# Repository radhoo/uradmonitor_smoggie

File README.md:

# uradmonitor_smoggie
SMOGGIE is an ultra-low cost automated air quality monitor with a rain proof enclosure and a simple mount system to make installation easy. 

This repo includes all the blueprints needed to build Smoggie:
1) PCB shield for Wemos D1 Wifi module , plus a series of sensors: 
Particulate Matter: Plantower PMSA003, PMS5003, PMS6003, PMS7003, Winsen ZH03A, Cubic PM2009
CO2: Winsen MH-Z19B, Cubic CM1106, Mixsen 6010 NDIR CO2 sensors
Gas: Winsen ZE03
2) Code, Arduino compatible, including local webserver, HTTP Client and all the drivers for the sensors supported
3) 3d Printable enclosure (Either Filament/FDM or Resin/SLA)

See also:
- the [uRADMonitor SMOGGIE-PM](https://www.uradmonitor.com/products/#docs-6) product page, click on tab "Smoggie PM"
- [Technical Datasheet](https://www.uradmonitor.com/wp-content/uploads/2021/08/datasheet_smoggie_v5_compressed.pdf)

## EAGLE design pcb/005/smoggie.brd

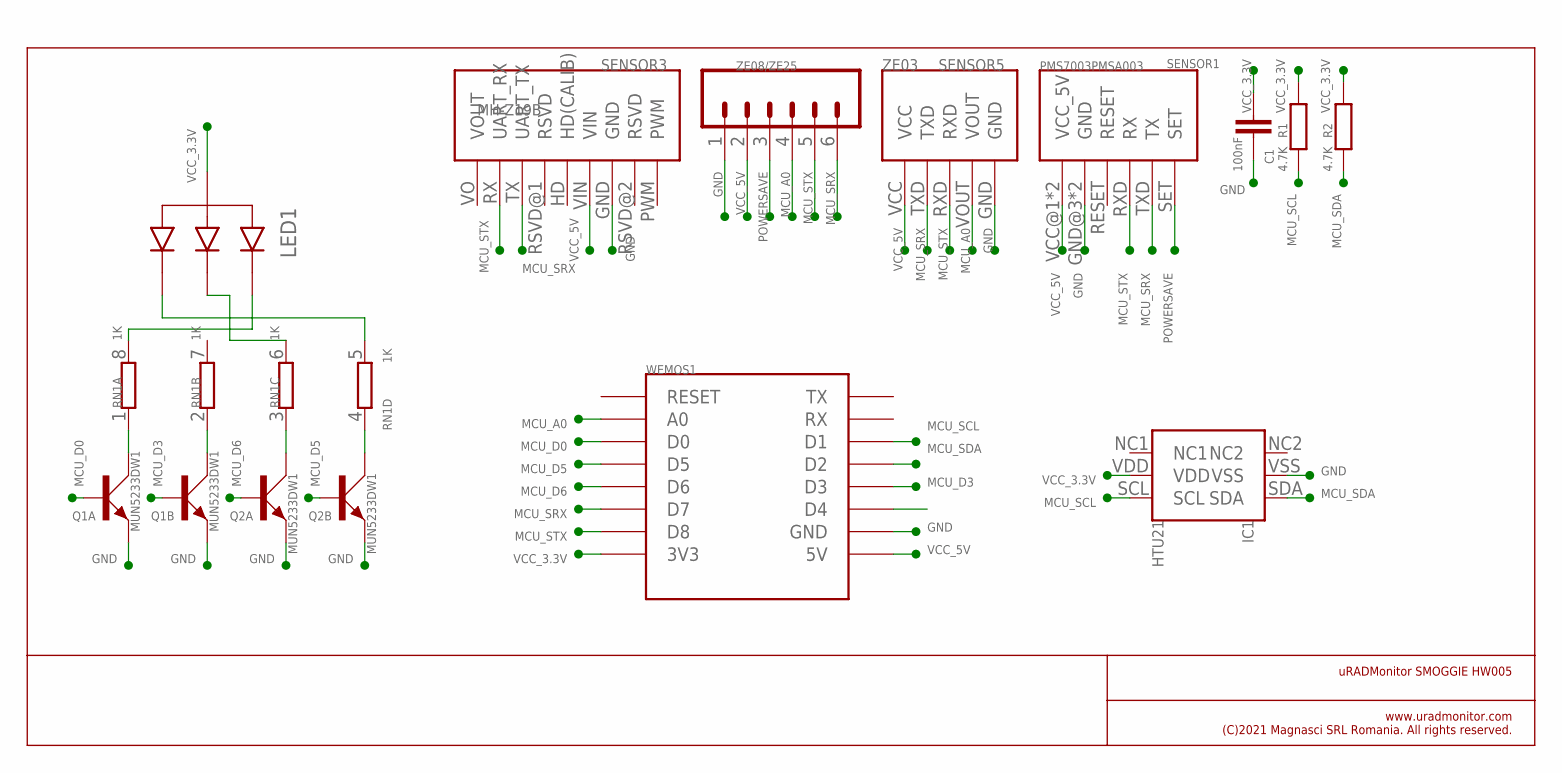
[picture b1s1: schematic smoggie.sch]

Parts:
C1: 100nF; C0603
IC1: HTU21; SHT21
LED1: LED_1615_RGB_CA; 1615_LED_CA
Q1, Q2: MUN5233DW1; SOT363_PHILIPS
R1, R2: 4.7K; R0603
RN1: 1K; 0603-ARC
SENSOR1: PMS7003PMSA003; PMSA003
SENSOR3: MH-Z19B
SENSOR5: ZE03
WEMOS1: 11; WEMOS-D1-MINI
ZE08/ZE25: M06SIP; 1X06

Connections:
GND: C1.1, IC1.VSS, Q1.1 (E), Q1.4 (E), Q2.1 (E), Q2.4 (E), SENSOR1.GND@3 (GND), SENSOR1.GND@4 (GND), SENSOR3.GND, SENSOR5.GND, WEMOS1.GND, ZE08/ZE25.1
MCU_A0: SENSOR5.VOUT, WEMOS1.A0, ZE08/ZE25.4
MCU_D0: Q1.2 (B), WEMOS1.D0
MCU_D3: Q1.5 (B), WEMOS1.D3
MCU_D5: Q2.5 (B), WEMOS1.D5
MCU_D6: Q2.2 (B), WEMOS1.D6
MCU_SCL: IC1.SCL, R1.2, WEMOS1.D1
MCU_SDA: IC1.SDA, R2.2, WEMOS1.D2
MCU_SRX: SENSOR1.TXD (TX), SENSOR3.TX (UART_TX), SENSOR5.TXD, WEMOS1.D7, ZE08/ZE25.6
MCU_STX: SENSOR1.RXD (RX), SENSOR3.RX (UART_RX), SENSOR5.RXD, WEMOS1.D8, ZE08/ZE25.5
unnamed: LED1.P$4 (P4_BLUE), RN1.8 (2)
unnamed: LED1.P$3 (P3_GREEN), RN1.6 (2)
unnamed: Q1.6 (C), RN1.1
unnamed: Q1.3 (C), RN1.2 (1)
unnamed: Q2.6 (C), RN1.3 (1)
unnamed: Q2.3 (C), RN1.4 (1)
unnamed: LED1.P$2 (P2_RED), RN1.5 (2)
POWERSAVE: SENSOR1.SET, ZE08/ZE25.3
VCC_3.3V: C1.2, IC1.VDD, LED1.P$1 (P1_CA), R1.1, R2.1, WEMOS1.3V3
VCC_5V: SENSOR1.VCC@1 (VCC_5V), SENSOR1.VCC@2 (VCC_5V), SENSOR3.VIN, SENSOR5.VCC, WEMOS1.5V, ZE08/ZE25.2

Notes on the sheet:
uRADMonitor SMOGGIE HW005
www.uradmonitor.com (C)2021 Magnasci SRL Romania. All rights reserved.

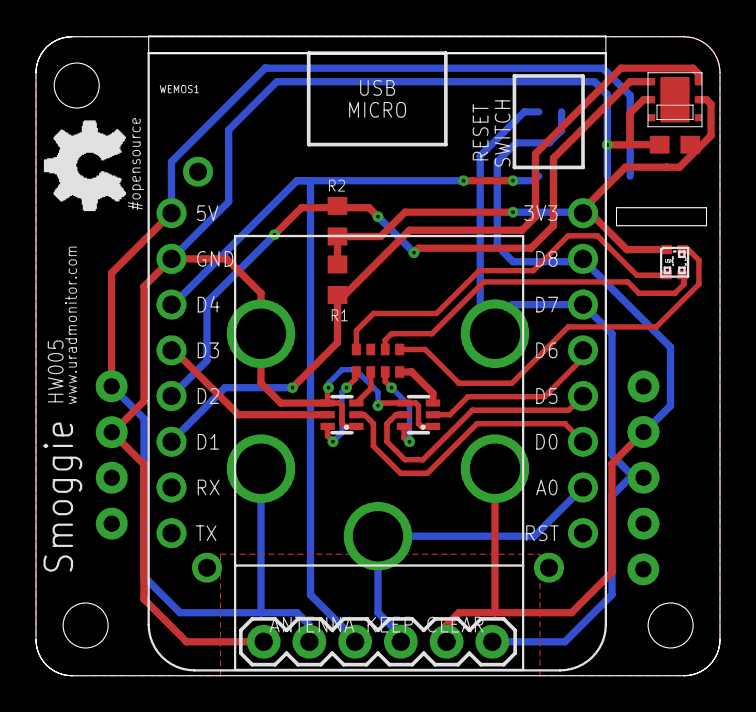
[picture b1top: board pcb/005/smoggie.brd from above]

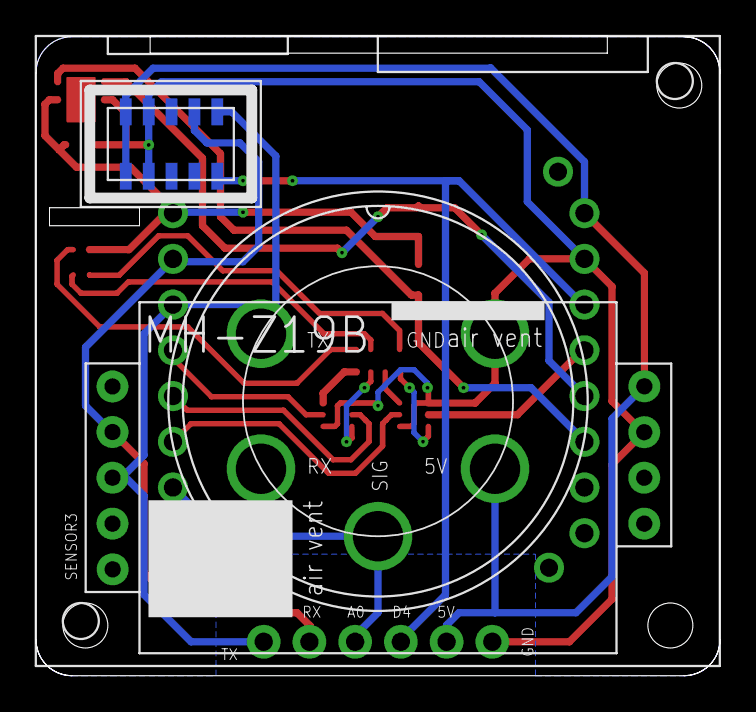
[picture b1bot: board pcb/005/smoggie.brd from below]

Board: 2 copper layers, 38.0 x 35.5 mm, 13 parts (3 on the bottom side), 20 nets.

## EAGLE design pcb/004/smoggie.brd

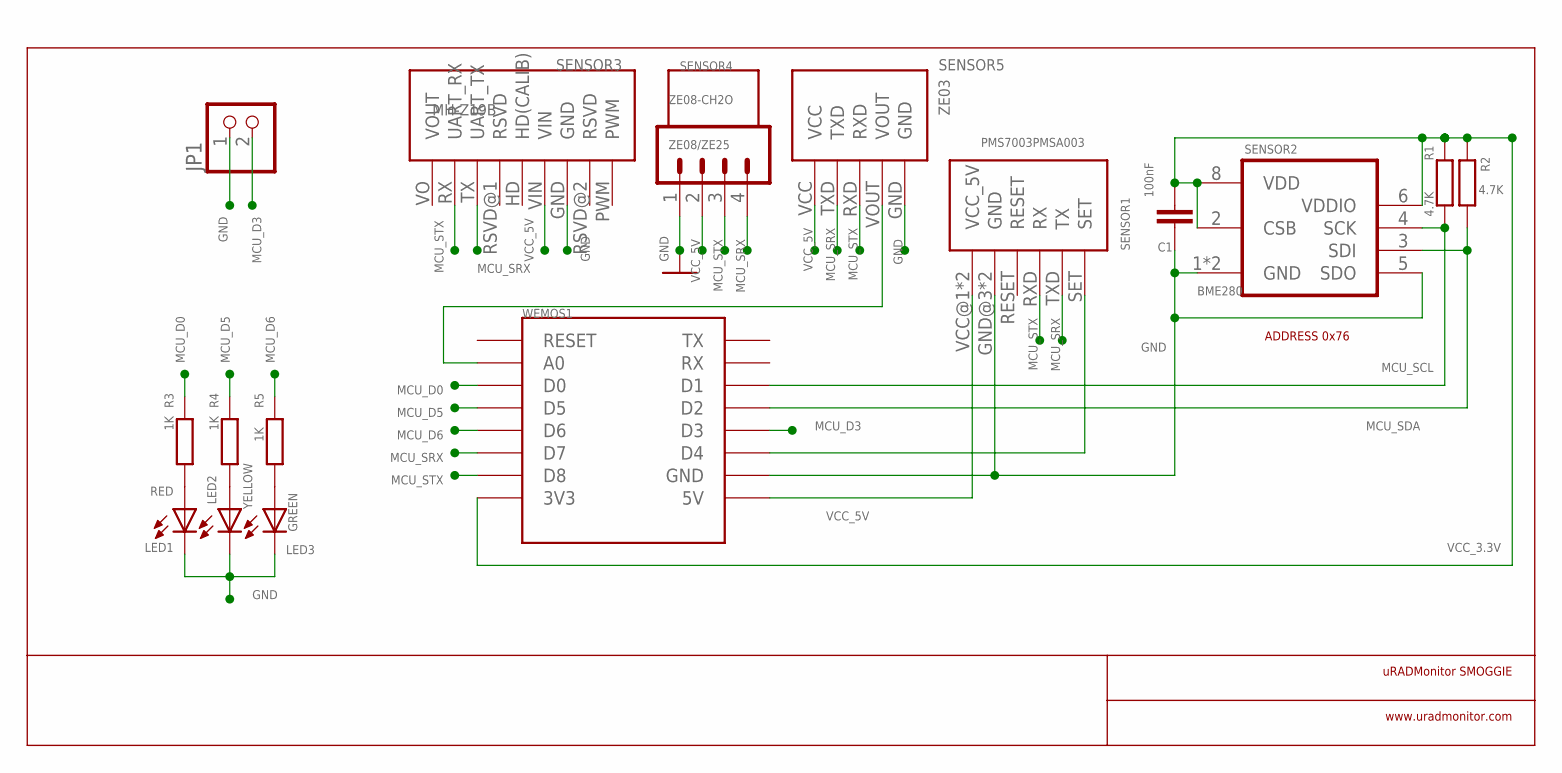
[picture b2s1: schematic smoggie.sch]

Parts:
C1: 100nF; C0603
JP1: PINHD-1X2; 1X02
LED1: RED; SML0603
LED2: YELLOW; SML0603
LED3: GREEN; SML0603
R1, R2: 4.7K; R0603
R3, R4, R5: 1K; R0603
SENSOR1: PMS7003PMSA003; PMSA003
SENSOR2: BME280
SENSOR3: MH-Z19B
SENSOR4: ZE08-CH2O; ZE08-CH2O_SENSOR
SENSOR5: ZE03
WEMOS1: 11; WEMOS-D1-MINI
ZE08/ZE25: M041X04_NO_SILK; 1X04_NO_SILK

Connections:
GND: C1.1, JP1.1, LED1.C, LED2.C, LED3.C, SENSOR1.GND@3 (GND), SENSOR1.GND@4 (GND), SENSOR2.1 (GND), SENSOR2.5 (SDO), SENSOR2.7 (GND), SENSOR3.GND, SENSOR5.GND, WEMOS1.GND, ZE08/ZE25.1
MCU_D0: R3.1, WEMOS1.D0
MCU_D3: JP1.2, WEMOS1.D3
MCU_D5: R4.1, WEMOS1.D5
MCU_D6: R5.1, WEMOS1.D6
MCU_SCL: R1.2, SENSOR2.4 (SCK), WEMOS1.D1
MCU_SDA: R2.2, SENSOR2.3 (SDI), WEMOS1.D2
MCU_SRX: SENSOR1.TXD (TX), SENSOR3.TX (UART_TX), SENSOR5.TXD, WEMOS1.D7, ZE08/ZE25.4
MCU_STX: SENSOR1.RXD (RX), SENSOR3.RX (UART_RX), SENSOR5.RXD, WEMOS1.D8, ZE08/ZE25.3
unnamed: LED2.A, R4.2
unnamed: LED3.A, R5.2
unnamed: SENSOR5.VOUT, WEMOS1.A0
unnamed: SENSOR1.SET, WEMOS1.D4
unnamed: LED1.A, R3.2
VCC_3.3V: C1.2, R1.1, R2.1, SENSOR2.2 (CSB), SENSOR2.6 (VDDIO), SENSOR2.8 (VDD), WEMOS1.3V3
VCC_5V: SENSOR1.VCC@1 (VCC_5V), SENSOR1.VCC@2 (VCC_5V), SENSOR3.VIN, SENSOR5.VCC, WEMOS1.5V, ZE08/ZE25.2

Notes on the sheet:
ADDRESS 0x76
uRADMonitor SMOGGIE
www.uradmonitor.com

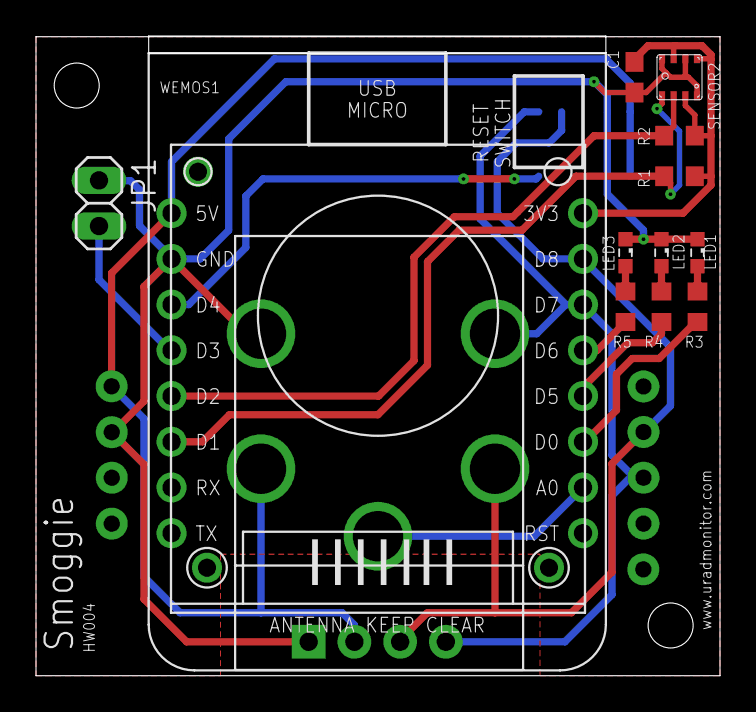
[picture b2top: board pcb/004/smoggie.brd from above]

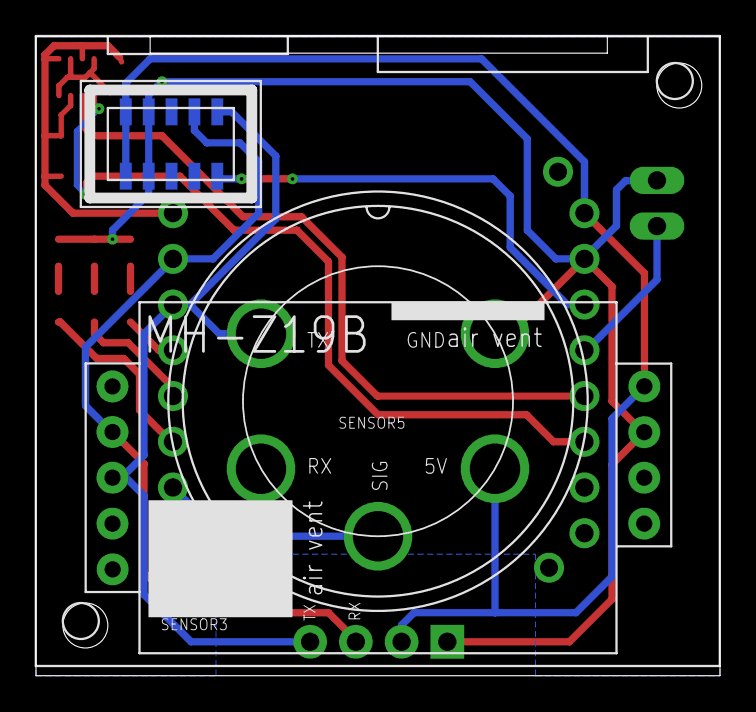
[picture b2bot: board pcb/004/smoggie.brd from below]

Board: 2 copper layers, 38.0 x 35.5 mm, 17 parts (3 on the bottom side), 16 nets.

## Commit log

2021-05-19 first release
2021-08-05 versioning + cc licensing
2022-04-16 Fix image link
2022-04-16 And link to datasheet
2022-08-02 hardware v5 smoggie-kit

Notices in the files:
parts and their libraries:
sparkfun-connectors: Licensing: CC v3.0 Share-Alike You are welcome to use this library for commercial purposes.
sensirion-sht-sensors: Library created By: GreyhoundPCBDesign ©2020
CC BY 4.0 - Creative Commons 4.0 https://creativecommons.org/licenses/by/4.0/deed.en
